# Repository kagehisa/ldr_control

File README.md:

# ldr_control

This repository holds the kicad project, designed to serve as a IIC controlable clone note LDR switch.
It is designed to replace the rotary switch included in th eclone note LDR kit.

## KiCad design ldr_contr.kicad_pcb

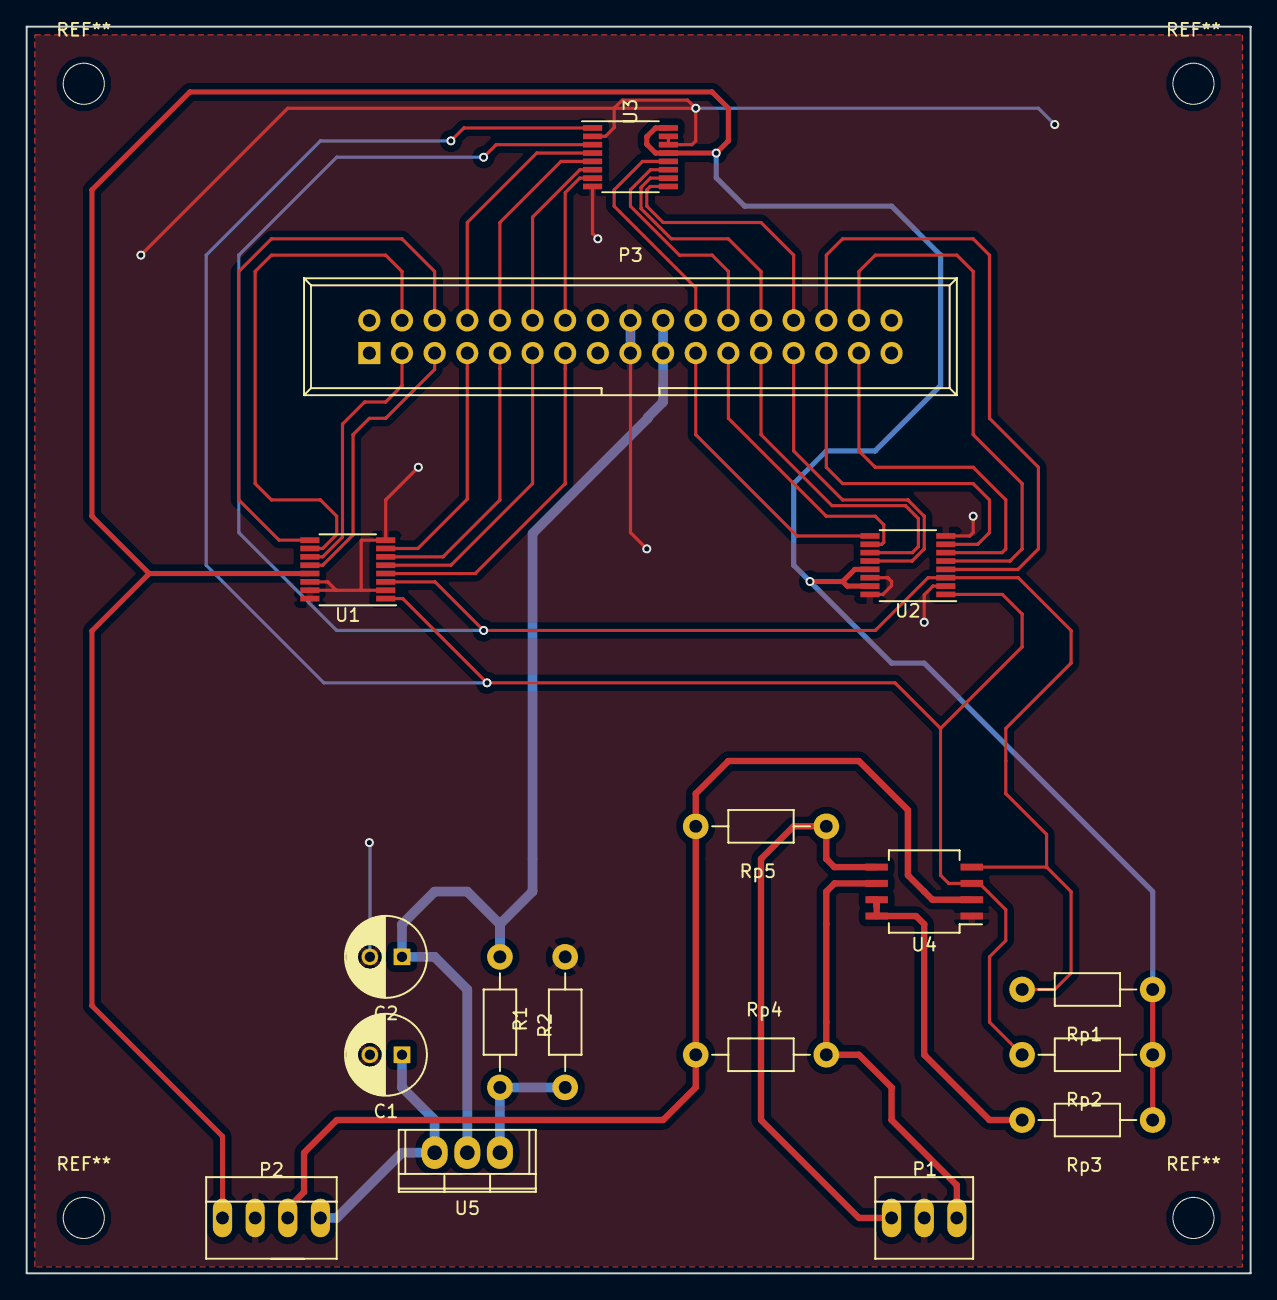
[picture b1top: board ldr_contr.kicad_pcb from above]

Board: 2 copper layers, 95.2 x 97.0 mm, 17 parts (0 on the bottom side), 35 nets.

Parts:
C1, C2: 100uF / 25V; C_Radial_D6.3_L11.2_P2.5
P1: CONN_01X03; PINHEAD1-3
P2: CONN_01X04; PINHEAD1-4
P3: CONN_02X17; IDC_Header_Straight_34pins
R1: 287R; Resistor_Horizontal_RM10mm
R2: 1kR; Resistor_Horizontal_RM10mm
Rp1, Rp2, Rp4, Rp5: 4.7k; Resistor_Horizontal_RM10mm
Rp3: 200k; Resistor_Horizontal_RM10mm
U1, U2, U3: ADG728; TSSOP-16_4.4x5mm_Pitch0.65mm
U4: PCA9306; SO-8_5.3x6.2mm_Pitch1.27mm
U5: LM317_3PinPackage; TO-220

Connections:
/SCL: P1.3, Rp4.2, U4.6
GND: C1.2, C2.2, P1.2, P2.2, P3.17, P3.18, R1.2, U1.2, U1.8, U1.14, U1.15, U1.16, U2.2, U2.8, U2.14, U2.16, U3.2, U3.8, U3.14, U3.15, U4.1
unnamed: C1.1, P2.4, U5.3
unnamed: C2.1, P3.19, P3.20, R2.1, U5.2
unnamed: P1.1, Rp5.1, U4.5
unnamed: P2.1, Rp1.1, Rp2.1, Rp3.1, U1.13, U2.13, U2.15, U3.13, U3.16
unnamed: P2.3, Rp4.1, Rp5.2, U4.2
unnamed: P3.3, U1.11
unnamed: P3.4, U1.10
unnamed: P3.5, U1.12
unnamed: P3.6, U1.9
unnamed: P3.7, U1.7
unnamed: P3.8, U3.4
unnamed: P3.9, U1.6
unnamed: P3.10, U3.5
unnamed: P3.11, U1.5
unnamed: P3.12, U3.6
unnamed: P3.13, U1.4
unnamed: P3.14, U3.7
unnamed: P3.21, U2.9
unnamed: P3.22, U3.12
unnamed: P3.23, U2.10
unnamed: P3.24, U3.11
unnamed: P3.25, U2.11
unnamed: P3.26, U3.10
unnamed: P3.27, U2.12
unnamed: P3.28, U3.9
unnamed: P3.29, U2.7
unnamed: P3.30, U2.4
unnamed: P3.31, U2.6
unnamed: P3.32, U2.5
unnamed: R1.1, R2.2, U5.1
unnamed: Rp1.2, U1.3, U2.3, U3.3, U4.4
unnamed: Rp2.2, U1.1, U2.1, U3.1, U4.3
unnamed: Rp3.2, U4.7, U4.8

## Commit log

2018-04-10 latest changes including pegel converter
2018-04-10 removal of temp files
2018-04-10 schematic finalized
2018-04-11 board ready
2018-04-12 cleanup
2018-04-12 cleanup part two, next will be to transfer all the single lines from the adg728 to the idc into a bus for a more readable desing.
2018-04-13 fixed adg728 airwire for the D input to ground
2018-04-13 Minor fix for 5V power line
2020-03-16 kicad update to version 5, ADG728 is now using the defualt Library
2020-03-16 project cleanup. Upstream lib for ADG728 has a wrong pinout
2020-03-17 added preview picture
